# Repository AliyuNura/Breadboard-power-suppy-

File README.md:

# Breadboard-power-suppy-
This is a power supply to be feed by 12VDC power and supply a 42mm breadboard with 3.3V and 5V DC supply

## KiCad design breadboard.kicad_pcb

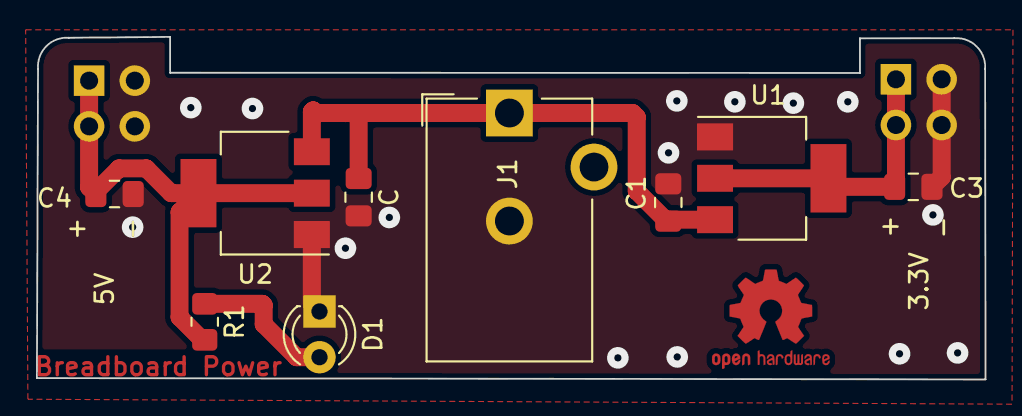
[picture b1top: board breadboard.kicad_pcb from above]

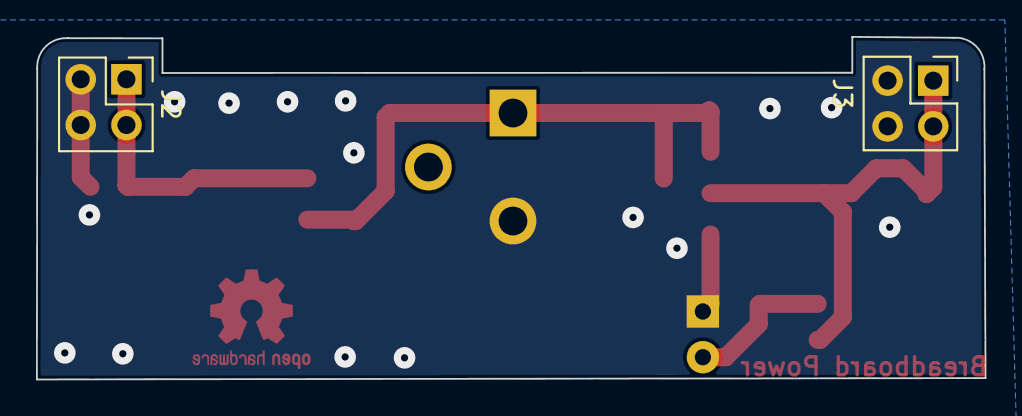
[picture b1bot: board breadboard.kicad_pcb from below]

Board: 2 copper layers, 52.7 x 19.0 mm, 11 parts (2 on the bottom side), 5 nets.

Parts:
C, C1: 10uf; C_0805_2012Metric_Pad1.18x1.45mm_HandSolder
C3, C4: 22uf; C_0805_2012Metric_Pad1.18x1.45mm_HandSolder
D1: LED; LED_D3.0mm
J1: PJ-102AH; BarrelJack_CUI_PJ-102AH_Horizontal
J2, J3: Conn_02x02_Odd_Even; PinHeader_2x02_P2.54mm_Vertical
R1: 1k; R_0805_2012Metric_Pad1.20x1.40mm_HandSolder
U1: AZ1117-3.3; SOT-223-3_TabPin2
U2: AZ1117-5.0; SOT-223-3_TabPin2

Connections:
GND: C.2, C1.2, C3.2, C4.2, D1.1 (K), J1.2, J2.3, J2.4, J3.3, J3.4, U1.1 (GND), U2.1 (GND)
unnamed: D1.2 (A), R1.1
unnamed: C3.1, J2.1, J2.2, U1.2 (VO)
unnamed: C4.1, J3.1, J3.2, R1.2, U2.2 (VO)
unnamed: C.1, C1.1, J1.1, U1.3 (VI), U2.3 (VI)

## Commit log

2022-09-13 breadboard power supply
